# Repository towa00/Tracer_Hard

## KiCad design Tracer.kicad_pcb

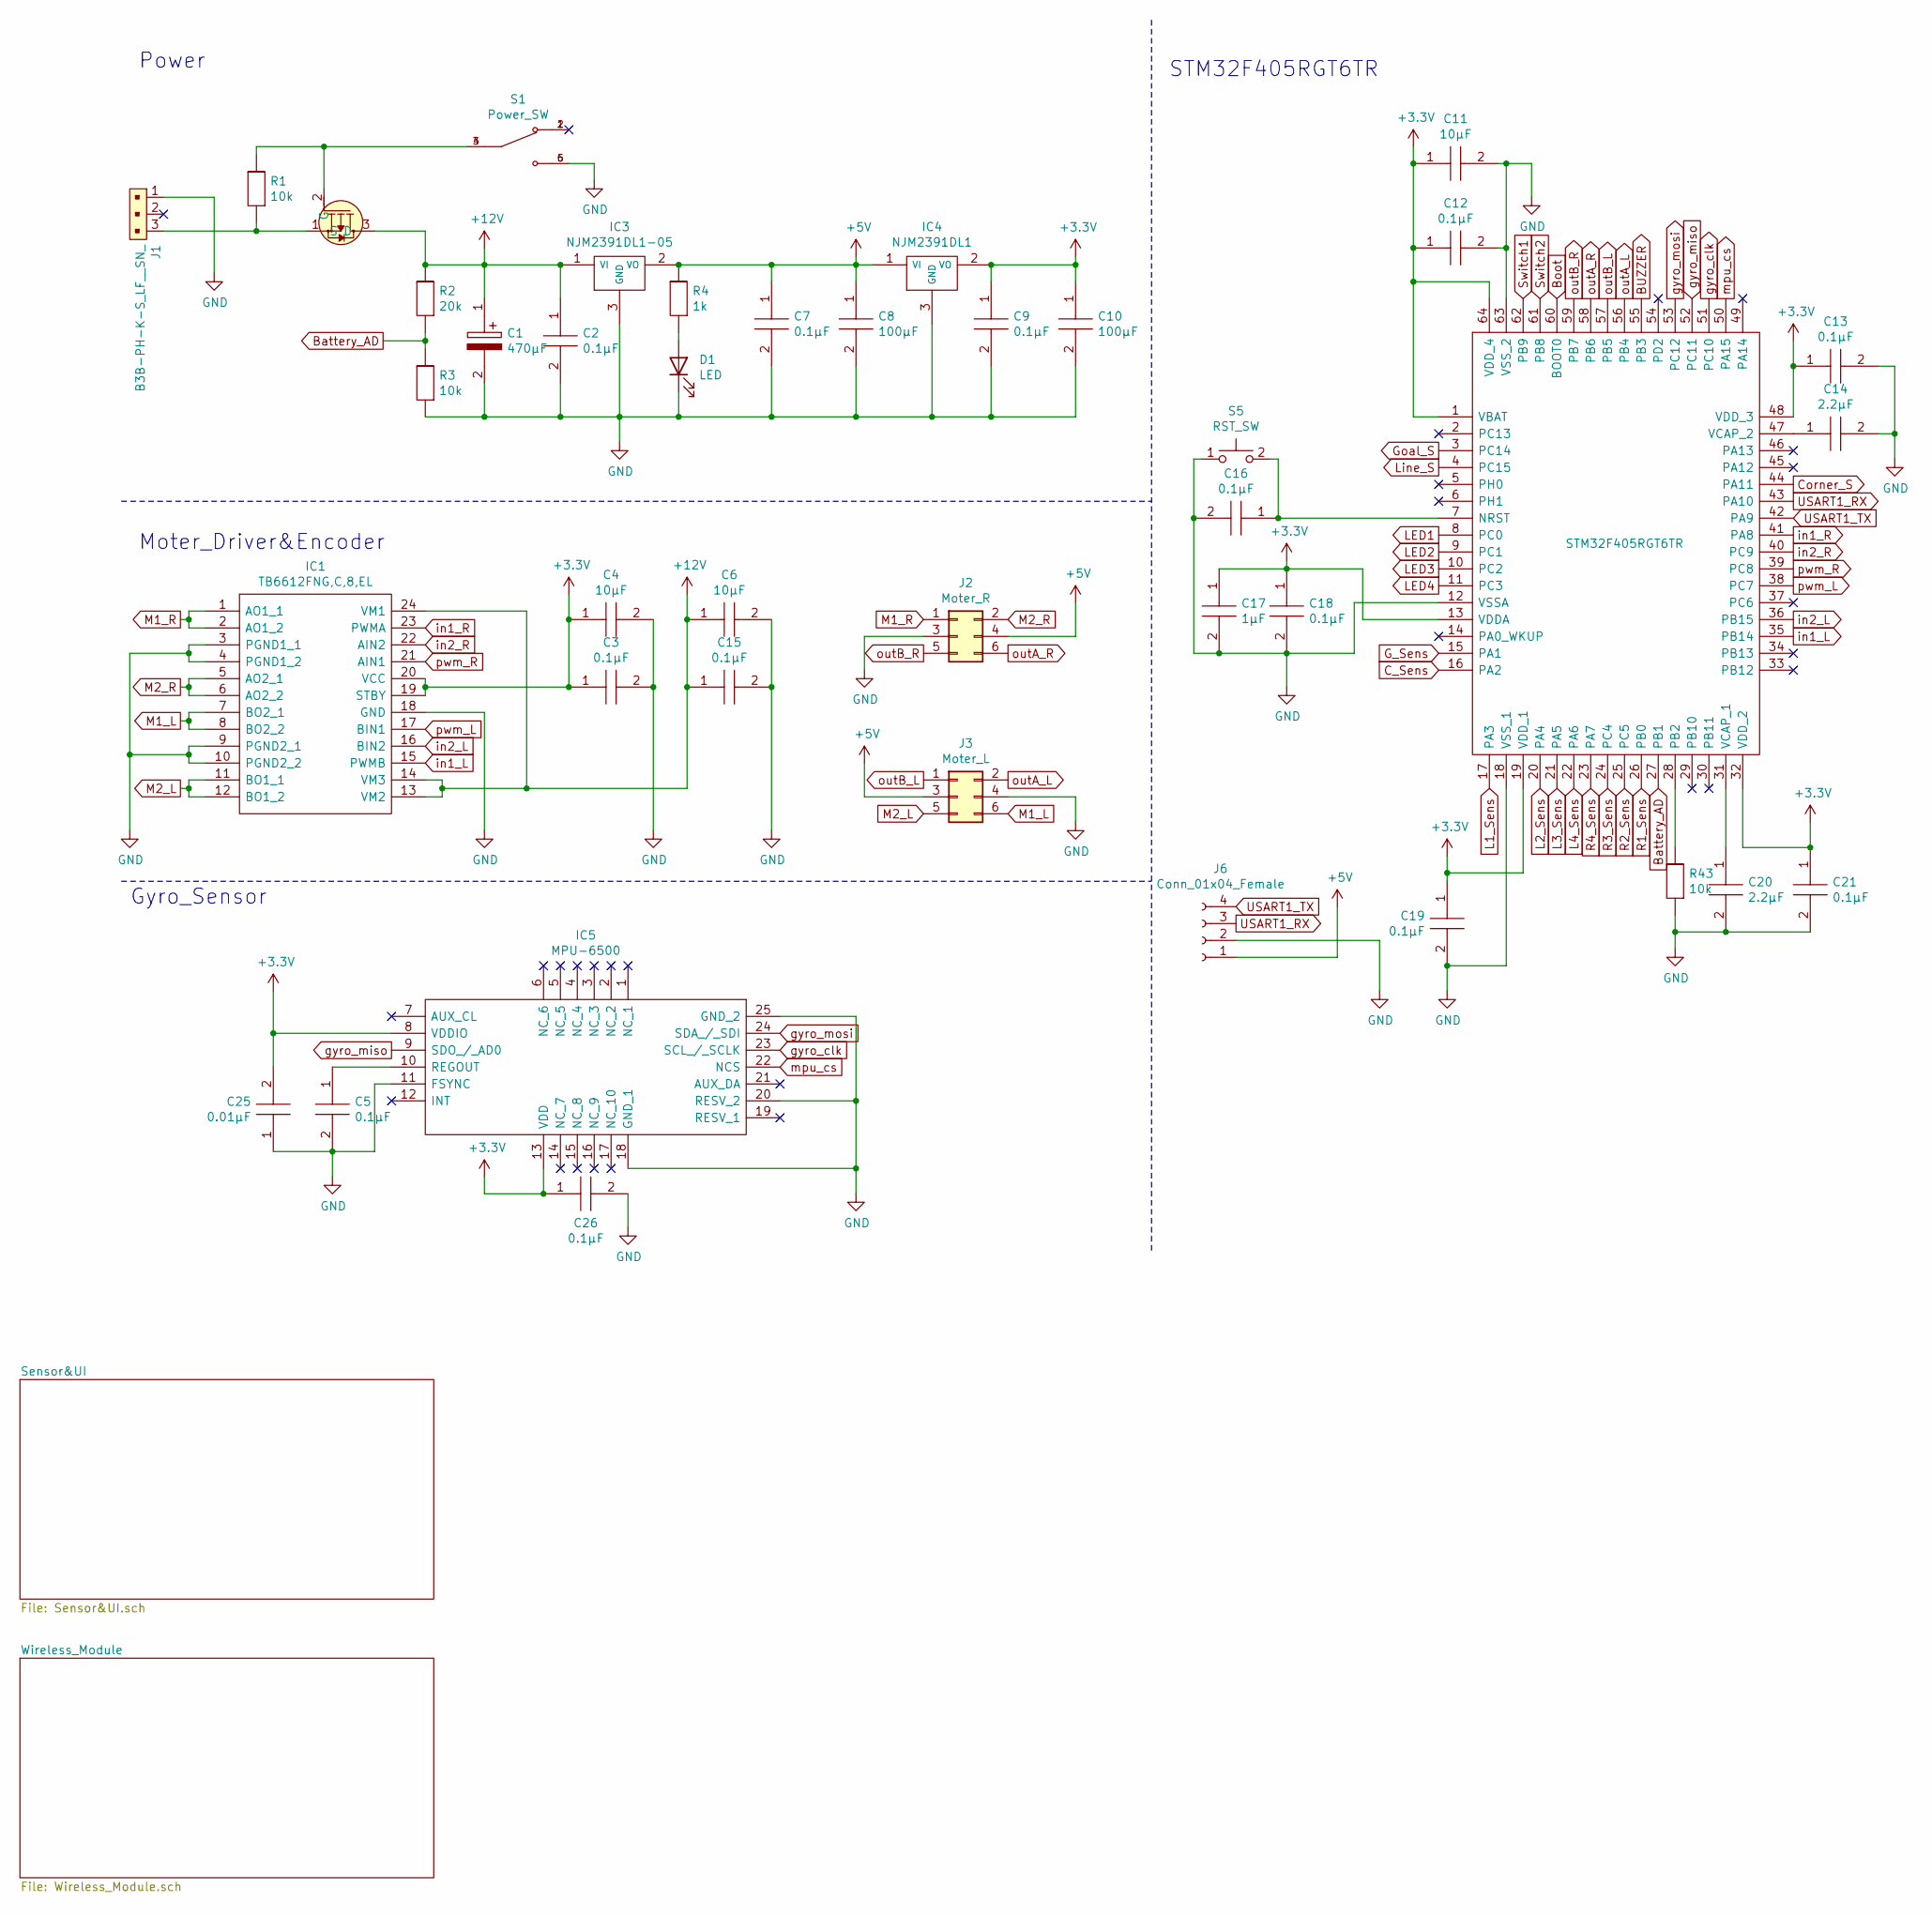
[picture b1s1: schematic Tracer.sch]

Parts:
C1: 470μF; CAPPRD500W65D1000H1300; Mouser Part Number 667-16SEPC470M
C2, C3, C5, C7, C9, C12, C13, C15, C16, C18, C19, C21, C26: 0.1μF; CAPC1608X90N; Mouser Part Number 81-GRM188R72A104KA35
C4, C6, C11: 10μF; CAPC1608X90N; Mouser Part Number 81-GRM188R6YA106MA3D
C8, C10: 100μF; CAPC3216X180N; Mouser Part Number 81-GRM31CR61A107MA8K
C14, C20: 2.2μF; CAPC1608X90N; Mouser Part Number 81-GRM188R6YA106MA3D
C17: 1μF; CAPC1608X90N; Mouser Part Number 81-GRM188R72A104KA35
C25: 0.01μF; CAPC1608X90N; Mouser Part Number 81-GRM188R72A104KA35
D1: LED; LED_0805_2012Metric
IC1: TB6612FNG,C,8,EL; SOP65P760X160-24N; Mouser Part Number 757-TB6612FNGC8EL
IC2: FDS6576; SOIC127P600X175-8N; Mouser Part Number 512-FDS6576
IC3: NJM2391DL1-05; TO-252-3-L1; Mouser Part Number 513-NJM2391DL133-TE1
IC4: NJM2391DL1; TO-252-3-L1; Mouser Part Number 513-NJM2391DL133-TE1
IC5: MPU-6500; QFN40P300X300X95-25N-D; Mouser Part Number 410-MPU-6500
IC6: STM32F405RGT6TR; QFP50P1200X1200X160-64N; Mouser Part Number 511-STM32F405RGT6TR
J1: B3B-PH-K-S_LF__SN_; PinHeader_1x3_P2mm_Drill1mm; MPN B3B-PH-K-S(LF)(SN); Digi-Key_PN 455-1705-ND
J2: Moter_R; PinHeader_2x03_P2.54mm_Vertical
J3: Moter_L; PinHeader_2x03_P2.54mm_Vertical
J6: Conn_01x04_Female; PinSocket_1x04_P2.54mm_Vertical
R1, R3, R43: 10k; RESC2012X50N
R2: 20k; RESC2012X50N
R4: 1k; RESC2012X50N
S1: Power_SW; SW_MHSS1104; PARTREV A
S5: RST_SW; SMT_4.2X3.2_; Mouser Part Number 688-SKRPACE010

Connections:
+3V3: C3.1, C4.1, C9.1, C10.1, C11.1, C12.1, C13.1, C17.1, C18.1, C19.1, C21.1, C25.2, C26.1, IC1.19 (STBY), IC1.20 (VCC), IC4.2 (VO), IC5.8 (VDDIO), IC5.13 (VDD), IC6.1 (VBAT), IC6.13 (VDDA), IC6.19 (VDD_1), IC6.32 (VDD_2), IC6.48 (VDD_3), IC6.64 (VDD_4); also elsewhere on the board
+5V: C7.1, C8.1, IC3.2 (VO), IC4.1 (VI), J2.4, J3.3, J6.1, R4.1; also elsewhere on the board
+12V: C1.1, C2.1, C6.1, C15.1, IC1.13 (VM2), IC1.14 (VM3), IC1.24 (VM1), IC2.3 (D), IC3.1 (VI), R2.1
BUZZER: IC6.55 (PB3); also elsewhere on the board
Battery_AD: IC6.27 (PB1), R2.2, R3.1
Boot: IC6.60 (BOOT0), IC6.61 (PB8); also elsewhere on the board
C_Sens: IC6.16 (PA2); also elsewhere on the board
Corner_S: IC6.44 (PA11); also elsewhere on the board
GND: C1.2, C2.2, C3.2, C4.2, C5.2, C6.2, C7.2, C8.2, C9.2, C10.2, C11.2, C12.2, C13.2, C14.2, C15.2, C16.2, C17.2, C18.2, C19.2, C20.2, C21.2, C25.1, C26.2, D1.1 (K), IC1.3 (PGND1_1), IC1.4 (PGND1_2), IC1.9 (PGND2_1), IC1.10 (PGND2_2), IC1.18 (GND), IC3.3 (GND), IC4.3 (GND), IC5.11 (FSYNC), IC5.18 (GND_1), IC5.20 (RESV_2), IC5.25 (GND_2), IC6.12 (VSSA), IC6.18 (VSS_1), IC6.63 (VSS_2), J1.1, J2.3, J3.4, J6.2, R3.2, R43.2, S1.5, S1.6, S5.1; also elsewhere on the board
G_Sens: IC6.15 (PA1); also elsewhere on the board
Goal_S: IC6.3 (PC14); also elsewhere on the board
L1_Sens: IC6.17 (PA3); also elsewhere on the board
L2_Sens: IC6.20 (PA4); also elsewhere on the board
L3_Sens: IC6.21 (PA5); also elsewhere on the board
L4_Sens: IC6.22 (PA6); also elsewhere on the board
LED1: IC6.8 (PC0); also elsewhere on the board
LED2: IC6.9 (PC1); also elsewhere on the board
LED3: IC6.10 (PC2); also elsewhere on the board
LED4: IC6.11 (PC3); also elsewhere on the board
Line_S: IC6.4 (PC15); also elsewhere on the board
M1_L: IC1.7 (BO2_1), IC1.8 (BO2_2), J3.6
M1_R: IC1.1 (AO1_1), IC1.2 (AO1_2), J2.1
M2_L: IC1.11 (BO1_1), IC1.12 (BO1_2), J3.5
M2_R: IC1.5 (AO2_1), IC1.6 (AO2_2), J2.2
unnamed: C5.1, IC5.10 (REGOUT)
unnamed: C14.1, IC6.47 (VCAP_2)
unnamed: C16.1, IC6.7 (NRST), S5.2
unnamed: C20.1, IC6.31 (VCAP_1)
unnamed: D1.2 (A), R4.2
unnamed: IC2.1 (S), J1.3, R1.2
unnamed: IC2.2 (G), R1.1, S1.3, S1.4
unnamed: IC6.28 (PB2), R43.1
unnamed: S1.1, S1.2
R1_Sens: IC6.26 (PB0); also elsewhere on the board
R2_Sens: IC6.25 (PC5); also elsewhere on the board
R3_Sens: IC6.24 (PC4); also elsewhere on the board
R4_Sens: IC6.23 (PA7); also elsewhere on the board
Switch1: IC6.62 (PB9); also elsewhere on the board
USART1_RX: IC6.43 (PA10), J6.3
USART1_TX: IC6.42 (PA9), J6.4
gyro_clk: IC5.23 (SCL_/_SCLK), IC6.51 (PC10)
gyro_miso: IC5.9 (SDO_/_AD0), IC6.52 (PC11)
gyro_mosi: IC5.24 (SDA_/_SDI), IC6.53 (PC12)
in1_L: IC1.15 (PWMB), IC6.35 (PB14)
in1_R: IC1.23 (PWMA), IC6.41 (PA8)
in2_L: IC1.16 (BIN2), IC6.36 (PB15)
in2_R: IC1.22 (AIN2), IC6.40 (PC9)
mpu_cs: IC5.22 (NCS), IC6.50 (PA15)
outA_L: IC6.56 (PB4), J3.2
outA_R: IC6.58 (PB6), J2.6
outB_L: IC6.57 (PB5), J3.1
outB_R: IC6.59 (PB7), J2.5
pwm_L: IC1.17 (BIN1), IC6.38 (PC7)
pwm_R: IC1.21 (AIN1), IC6.39 (PC8)

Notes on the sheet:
STM32F405RGT6TR
Gyro_Sensor
Moter_Driver&Encoder
Power

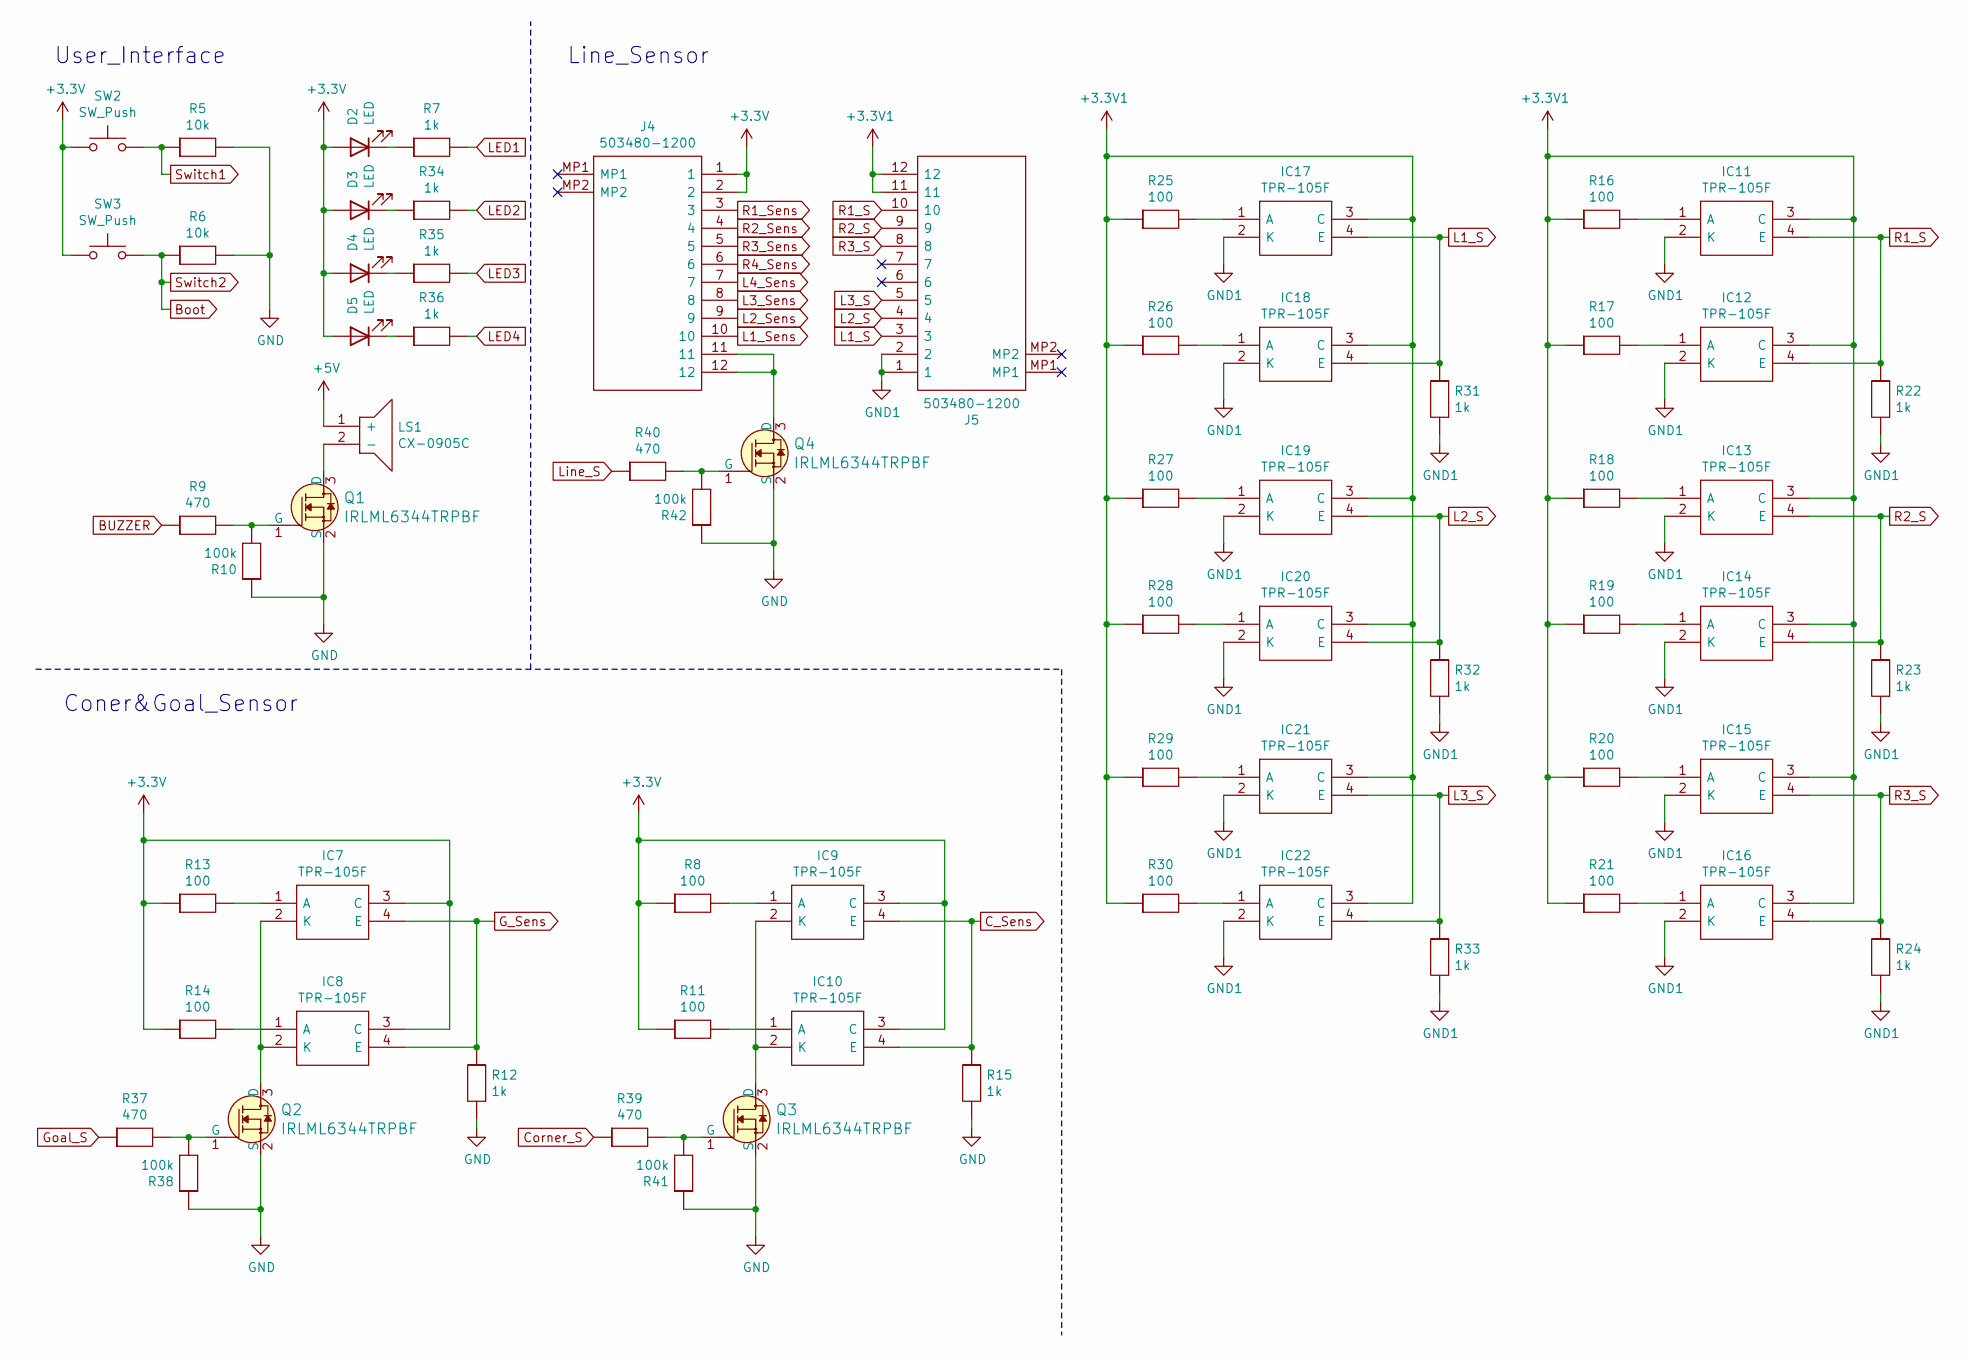
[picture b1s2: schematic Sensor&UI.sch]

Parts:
D2, D3, D4, D5: LED; LED_0805_2012Metric
IC7, IC8, IC9, IC10, IC11, IC12, IC13, IC14, IC15, IC16, IC17, IC18, IC19, IC20, IC21, IC22: TPR-105F; Mouser Part Number 512-QRE1113
J4, J5: 503480-1200; 5034801200; Mouser Part Number 538-503480-1200
LS1: CX-0905C; CX0905C; Mouser Part Number 490-CX-0905C
Q1, Q2, Q3, Q4: IRLML6344TRPBF; SOT-23-3; MPN IRLML6344TRPBF; Digi-Key_PN IRLML6344TRPBFCT-ND
R5, R6: 10k; RESC2012X50N
R7, R12, R15, R22, R23, R24, R31, R32, R33, R34, R35, R36: 1k; RESC2012X50N
R8, R11, R13, R14, R16, R17, R18, R19, R20, R21, R25, R26, R27, R28, R29, R30: 100; RESC2012X50N
R9, R37, R39, R40: 470; RESC2012X50N
R10, R38, R41, R42: 100k; RESC2012X50N
SW2, SW3: SW_Push; TVBP06-B043CW-B

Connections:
+3.3V1: IC11.3 (C), IC12.3 (C), IC13.3 (C), IC14.3 (C), IC15.3 (C), IC16.3 (C), IC17.3 (C), IC18.3 (C), IC19.3 (C), IC20.3 (C), IC21.3 (C), IC22.3 (C), J5.11, J5.12, R16.1, R17.1, R18.1, R19.1, R20.1, R21.1, R25.1, R26.1, R27.1, R28.1, R29.1, R30.1
+3V3: D2.2 (A), D3.2 (A), D4.2 (A), D5.2 (A), IC7.3 (C), IC8.3 (C), IC9.3 (C), IC10.3 (C), J4.1, J4.2, R8.1, R11.1, R13.1, R14.1, SW2.1, SW3.1; also elsewhere on the board
+5V: LS1.1 (+); also elsewhere on the board
BUZZER: R9.1; also elsewhere on the board
Boot: R6.1, SW3.2; also elsewhere on the board
C_Sens: IC9.4 (E), IC10.4 (E), R15.1; also elsewhere on the board
Corner_S: R39.1; also elsewhere on the board
GND: Q1.2 (S), Q2.2 (S), Q3.2 (S), Q4.2 (S), R5.2, R6.2, R10.1, R12.2, R15.2, R38.1, R41.1, R42.1; also elsewhere on the board
GND1: IC11.2 (K), IC12.2 (K), IC13.2 (K), IC14.2 (K), IC15.2 (K), IC16.2 (K), IC17.2 (K), IC18.2 (K), IC19.2 (K), IC20.2 (K), IC21.2 (K), IC22.2 (K), J5.1, J5.2, R22.2, R23.2, R24.2, R31.2, R32.2, R33.2
G_Sens: IC7.4 (E), IC8.4 (E), R12.1; also elsewhere on the board
Goal_S: R37.1; also elsewhere on the board
L1_S: IC17.4 (E), IC18.4 (E), J5.3, R31.1
L1_Sens: J4.10; also elsewhere on the board
L2_S: IC19.4 (E), IC20.4 (E), J5.4, R32.1
L2_Sens: J4.9; also elsewhere on the board
L3_S: IC21.4 (E), IC22.4 (E), J5.5, R33.1
L3_Sens: J4.8; also elsewhere on the board
L4_Sens: J4.7; also elsewhere on the board
LED1: R7.2; also elsewhere on the board
LED2: R34.2; also elsewhere on the board
LED3: R35.2; also elsewhere on the board
LED4: R36.2; also elsewhere on the board
Line_S: R40.1; also elsewhere on the board
unnamed: D2.1 (K), R7.1
unnamed: D3.1 (K), R34.1
unnamed: D4.1 (K), R35.1
unnamed: D5.1 (K), R36.1
unnamed: IC7.1 (A), R13.2
unnamed: IC7.2 (K), IC8.2 (K), Q2.3 (D)
unnamed: IC8.1 (A), R14.2
unnamed: IC9.1 (A), R8.2
unnamed: IC10.1 (A), R11.2
unnamed: IC9.2 (K), IC10.2 (K), Q3.3 (D)
unnamed: IC11.1 (A), R16.2
unnamed: IC12.1 (A), R17.2
unnamed: IC13.1 (A), R18.2
unnamed: IC14.1 (A), R19.2
unnamed: IC15.1 (A), R20.2
unnamed: IC16.1 (A), R21.2
unnamed: IC17.1 (A), R25.2
unnamed: IC18.1 (A), R26.2
unnamed: IC19.1 (A), R27.2
unnamed: IC20.1 (A), R28.2
unnamed: IC21.1 (A), R29.2
unnamed: IC22.1 (A), R30.2
unnamed: J4.11, J4.12, Q4.3 (D)
unnamed: LS1.2 (-), Q1.3 (D)
unnamed: Q1.1 (G), R9.2, R10.2
unnamed: Q2.1 (G), R37.2, R38.2
unnamed: Q3.1 (G), R39.2, R41.2
unnamed: Q4.1 (G), R40.2, R42.2
R1_S: IC11.4 (E), IC12.4 (E), J5.10, R22.1
R1_Sens: J4.3; also elsewhere on the board
R2_S: IC13.4 (E), IC14.4 (E), J5.9, R23.1
R2_Sens: J4.4; also elsewhere on the board
R3_S: IC15.4 (E), IC16.4 (E), J5.8, R24.1
R3_Sens: J4.5; also elsewhere on the board
R4_Sens: J4.6; also elsewhere on the board
Switch1: R5.1, SW2.2; also elsewhere on the board

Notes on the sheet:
User_Interface
Line_Sensor
Coner&Goal_Sensor

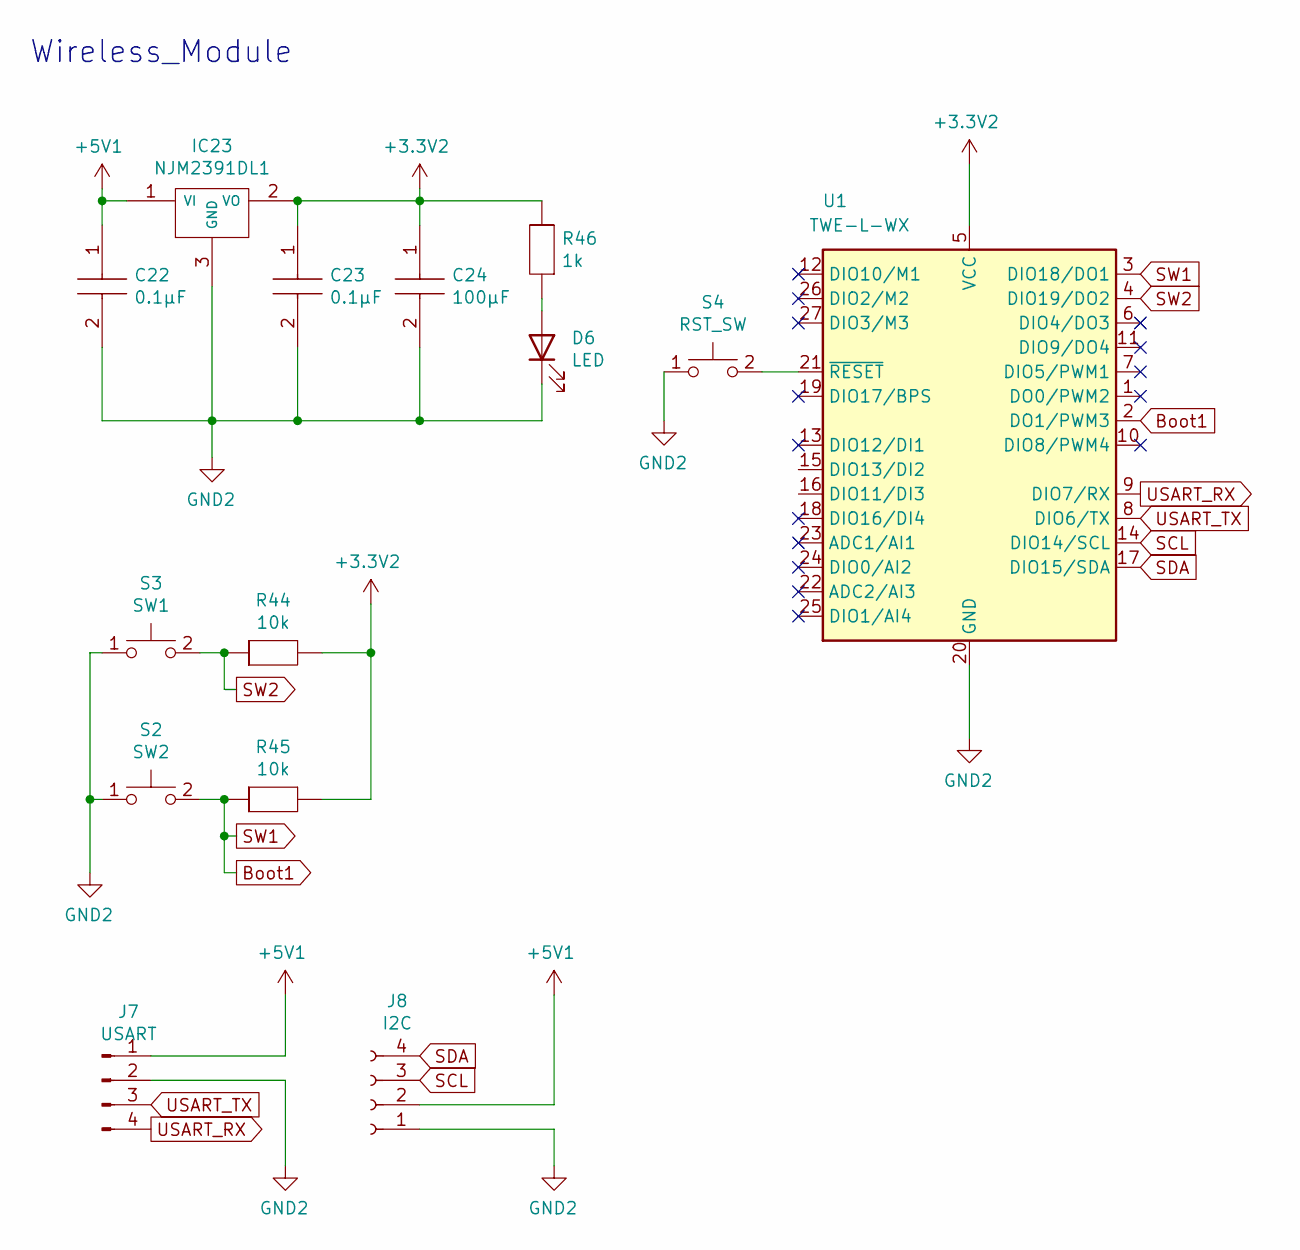
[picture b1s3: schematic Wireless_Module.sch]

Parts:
C22, C23: 0.1μF; CAPC1608X90N; Mouser Part Number 81-GRM188R72A104KA35
C24: 100μF; CAPC3216X180N; Mouser Part Number 81-GRM31CR61A107MA8K
D6: LED; LED_0805_2012Metric
IC23: NJM2391DL1; TO-252-3-L1; Mouser Part Number 513-NJM2391DL133-TE1
J7: USART; PinHeader_1x04_P2.54mm_Vertical
J8: I2C; PinSocket_1x04_P2.54mm_Vertical
R44, R45: 10k; RESC2012X50N
R46: 1k; RESC2012X50N
S2: SW2; SMT_4.2X3.2_; Mouser Part Number 688-SKRPACE010
S3: SW1; SMT_4.2X3.2_; Mouser Part Number 688-SKRPACE010
S4: RST_SW; SMT_4.2X3.2_; Mouser Part Number 688-SKRPACE010
U1: TWE-L-WX; MonoWireless_TWE-L-WX

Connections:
+3.3V_1: C23.1, C24.1, IC23.2 (VO), R44.2, R45.2, R46.1, U1.5 (VCC)
+5V1: C22.1, IC23.1 (VI), J7.1, J8.2
Boot1: R45.1, S2.2, U1.2 (DO1/PWM3), U1.3 (DIO18/DO1)
GND2: C22.2, C23.2, C24.2, D6.1 (K), IC23.3 (GND), J7.2, J8.1, S2.1, S3.1, S4.1, U1.20 (GND), U1.28 (GND), U1.30 (GND), U1.31 (GND), U1.32 (GND)
unnamed: D6.2 (A), R46.2
unnamed: S4.2, U1.21 (~RESET)
SCL: J8.3, U1.14 (DIO14/SCL)
SDA: J8.4, U1.17 (DIO15/SDA)
SW2: R44.1, S3.2, U1.4 (DIO19/DO2)
USART_RX: J7.4, U1.9 (DIO7/RX)
USART_TX: J7.3, U1.8 (DIO6/TX)

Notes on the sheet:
Wireless_Module

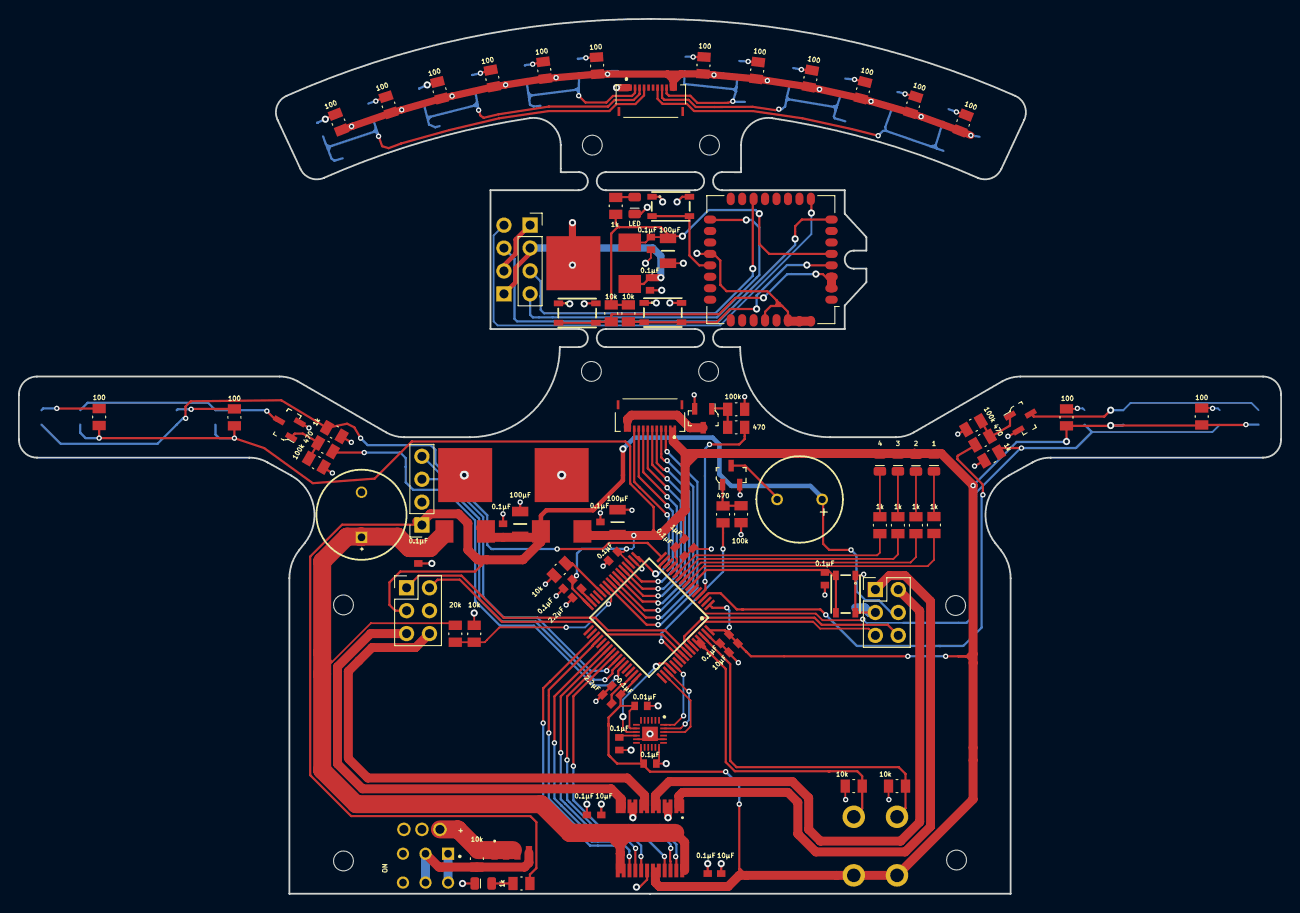
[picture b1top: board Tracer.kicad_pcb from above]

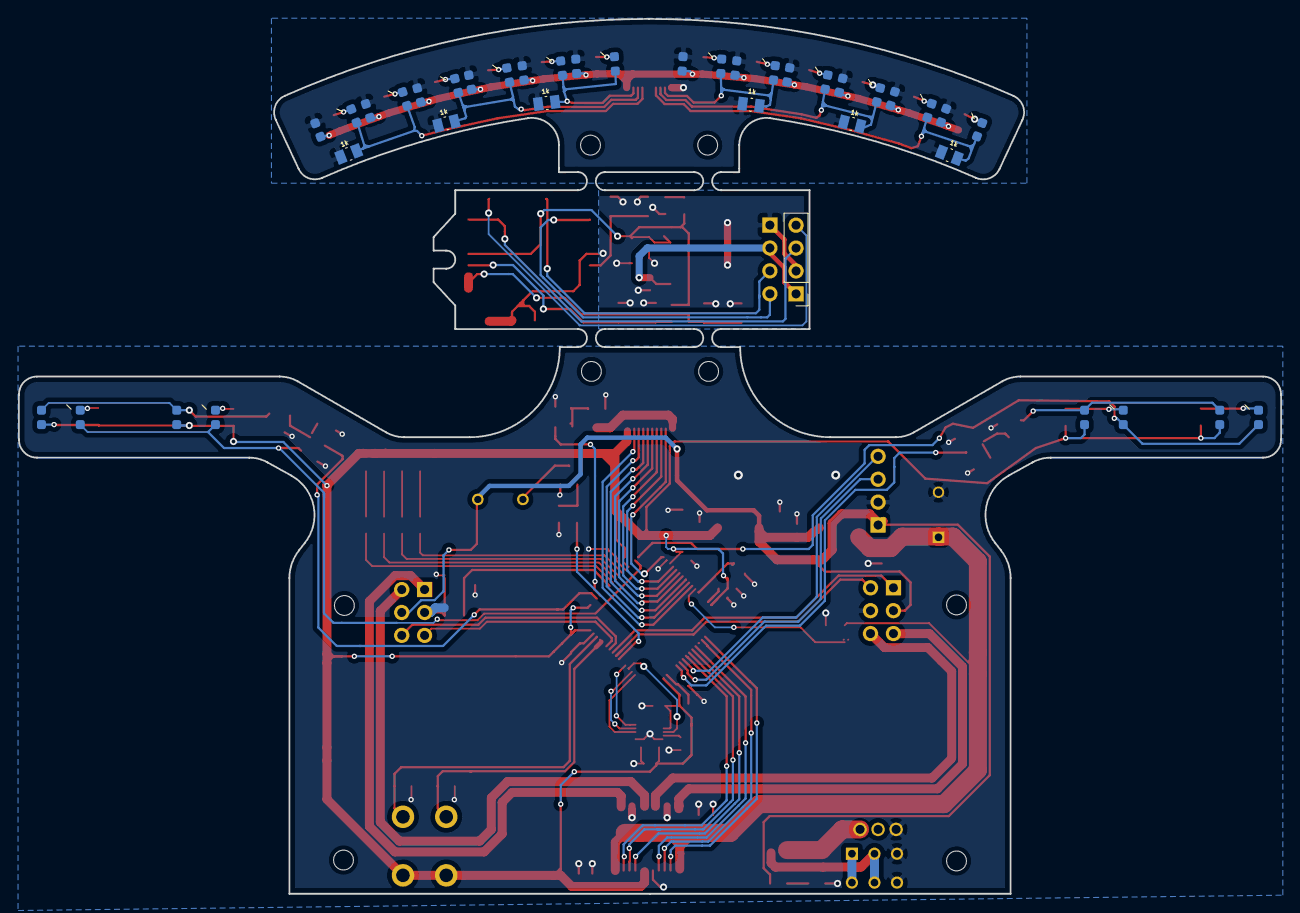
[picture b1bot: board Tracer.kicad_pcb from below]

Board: 2 copper layers, 140.0 x 97.0 mm, 130 parts (23 on the bottom side), 101 nets.

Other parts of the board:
M2, M2#2, M2#3, M2#4, M2#5, M2#6, M2#7, M2#8: MountingHole_2.2mm_M2

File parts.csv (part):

Reference, Quantity, Value, Footprint, Datasheet, Description, Height, Manufacturer_Name, Manufacturer_Part_Number, Mouser Part Number, Mouser Price/Stock, MANUFACTURER, MAXIMUM_PACKAGE_HEIGHT, PARTREV, STANDARD, Category, DK_Datasheet_Link, DK_Detail_Page, Digi-Key_PN, Family, MPN, Manufacturer, Status
C1 ,1,"470μF","CAPPRD500W65D1000H1300","http://industrial.panasonic.com/cdbs/www-data/pdf/AAB8000/AA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","Panasonic 470uF 16 V dc Polymer Aluminium Electrolytic Capacitor F13, OS-CON Series 5000h 10 x 13mm","13","Panasonic","16SEPC470M","667-16SEPC470M","https://www.mouser.co.uk/ProductDetail/Panasonic/16SEPC470M?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","","","","","","","","","","","",""
C8 C10 C24 ,3,"100μF","GRM31CR61A107MEA8K:CAPC3216X180N","http://www.murata.com/~/media/webrenewal/support/library/cat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","Multilayer Ceramic Capacitors MLCC - SMD/SMT 100UF    10V   20%        3216","1.8","Murata Electronics","GRM31CR61A107MEA8K","81-GRM31CR61A107MA8K","https://www.mouser.co.uk/ProductDetail/Murata-Electronics/GR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","","","","","","","","","","","",""
C14 C20 ,2,"2.2μF","CAPC1608X90N","http://componentsearchengine.com/Datasheets/1/GRM188R6YA106M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","Multilayer Ceramic Capacitors MLCC - SMD/SMT 0603 10uF 35volts *Derate Voltage/Temp","0.9","Murata Electronics","GRM188R6YA106MA73D","81-GRM188R6YA106MA3D","https://www.mouser.co.uk/ProductDetail/Murata-Electronics/GR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","","","","","","","","","","","",""
C2 C3 C5 C7 C9 C12 C13 C15 C16 C18 C19 C21 C22 C23 C26 ,15,"0.1μF","CAPC1608X90N","https://datasheet.datasheetarchive.com/originals/distributor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","Murata 0603 (1608M) 100nF MLCC 100V dc +/-10% SMD GRM188R72A104KA35D","0.9","Murata Electronics","GRM188R72A104KA35D","81-GRM188R72A104KA35","https://www.mouser.co.uk/ProductDetail/Murata-Electronics/GR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","","","","","","","","","","","",""
C17 ,1,"1μF","CAPC1608X90N","https://datasheet.datasheetarchive.com/originals/distributor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","Murata 0603 (1608M) 100nF MLCC 100V dc +/-10% SMD GRM188R72A104KA35D","0.9","Murata Electronics","GRM188R72A104KA35D","81-GRM188R72A104KA35","https://www.mouser.co.uk/ProductDetail/Murata-Electronics/GR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","","","","","","","","","","","",""
C25 ,1,"0.01μF","CAPC1608X90N","https://datasheet.datasheetarchive.com/originals/distributor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","Murata 0603 (1608M) 100nF MLCC 100V dc +/-10% SMD GRM188R72A104KA35D","0.9","Murata Electronics","GRM188R72A104KA35D","81-GRM188R72A104KA35","https://www.mouser.co.uk/ProductDetail/Murata-Electronics/GR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","","","","","","","","","","","",""
C4 C6 C11 ,3,"10μF","CAPC1608X90N","http://componentsearchengine.com/Datasheets/1/GRM188R6YA106M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","Multilayer Ceramic Capacitors MLCC - SMD/SMT 0603 10uF 35volts *Derate Voltage/Temp","0.9","Murata Electronics","GRM188R6YA106MA73D","81-GRM188R6YA106MA3D","https://www.mouser.co.uk/ProductDetail/Murata-Electronics/GR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","","","","","","","","","","","",""
D1 D6 ,2,"LED","LED_SMD:LED_0805_2012Metric","~"
D2 ,1,"LED1","LED_SMD:LED_1206_3216Metric","http://www.everlight.com/file/ProductFile/IR26-21C-L110-TR8.pdf"
D3 ,1,"LED2","LED_SMD:LED_1206_3216Metric","http://www.everlight.com/file/ProductFile/IR26-21C-L110-TR8.pdf"
D4 ,1,"LED3","LED_SMD:LED_1206_3216Metric","http://www.everlight.com/file/ProductFile/IR26-21C-L110-TR8.pdf"
D5 ,1,"LED4","LED_SMD:LED_1206_3216Metric","http://www.everlight.com/file/ProductFile/IR26-21C-L110-TR8.pdf"
IC1 ,1,"TB6612FNG,C,8,EL","TB6612FNG:SOP65P760X160-24N","http://toshiba.semicon-storage.com/info/docget.jsp?did=10660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","otor / Motion / Ignition Controllers & Drivers Brush Motor Driver IC","1.6","Toshiba","TB6612FNG,C,8,EL","757-TB6612FNGC8EL","https://www.mouser.co.uk/ProductDetail/Toshiba/TB6612FNGC8EL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","","","","","","","","","","","",""
IC7 IC8 IC9 IC10 IC11 IC12 IC13 IC14 IC15 IC16 IC17 IC18 IC19 IC20 IC21 IC22 ,16,"TPR-105F","TPR-105F:TPR-105F","https://www.onsemi.com/pub/Collateral/QRE1113-D.PDF","Miniature Reflective Object Sensor","1.7","onsemi","TPR-105","512-QRE1113","https://www.mouser.co.uk/ProductDetail/onsemi-Fairchild/QRE1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","","","","","","","","","","","",""
IC2 ,1,"FDS6576","FDS6576:SOIC127P600X175-8N","https://www.onsemi.com/pub/Collateral/751EB.PDF","FDS6576, P-channel MOSFET Transistor 11 A 20 V, 8-Pin SOIC","1.75","onsemi","FDS6576","512-FDS6576","https://www.mouser.co.uk/ProductDetail/ON-Semiconductor-Fair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","","","","","","","","","","","",""
IC3 ,1,"NJM2391DL1-05","NJM2391DL1-33-TE1:TO-252-3-L1","","LDO Voltage Regulators LDO","","New Japan Radio","NJM2391DL1-33-TE1","513-NJM2391DL133-TE1","https://www.mouser.co.uk/ProductDetail/NJR/NJM2391DL1-33-TE1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","","","","","","","","","","","",""
IC4 IC23 ,2,"NJM2391DL1","NJM2391DL1-33-TE1:TO-252-3-L1","","LDO Voltage Regulators LDO","","New Japan Radio","NJM2391DL1-33-TE1","513-NJM2391DL133-TE1","https://www.mouser.co.uk/ProductDetail/NJR/NJM2391DL1-33-TE1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","","","","","","","","","","","",""
IC5 ,1,"MPU-6500","MPU-6500:QFN40P300X300X95-25N-D","https://product.tdk.com/system/files/dam/doc/product/sensor/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","IMUs - Inertial Measurement Units 6-Axis MEMS MotionTracking  Device with DMP","0.95","TDK","MPU-6500","410-MPU-6500","https://www.mouser.co.uk/ProductDetail/TDK-InvenSense/MPU-65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","","","","","","","","","","","",""
IC6 ,1,"STM32F405RGT6TR","STM32F405RGT6TR:QFP50P1200X1200X160-64N","http://www.st.com/web/en/resource/technical/document/datashe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","STM32F405RGT6TR, 32 bit ARM Cortex M4 MCU 168MHz 1024 kB Flash, 192 kB RAM, 2xUSB CAN I2C 64-Pin LQFP","1.6","STMicroelectronics","STM32F405RGT6TR","511-STM32F405RGT6TR","https://www.mouser.co.uk/ProductDetail/STMicroelectronics/ST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","","","","","","","","","","","",""
J1 ,1,"B3B-PH-K-S_LF__SN_","digikey-footprints:PinHeader_1x3_P2mm_Drill1mm","http://www.jst-mfg.com/product/pdf/eng/ePH.pdf","CONN HEADER VERT 3POS 2MM","","","","","","","","","","Connectors, Interconnects","http://www.jst-mfg.com/product/pdf/eng/ePH.pdf","/product-detail/en/jst-sales-america-inc/B3B-PH-K-S(LF)(SN)/455-1705-ND/926612","455-1705-ND","Rectangular Connectors - Headers, Male Pins","B3B-PH-K-S(LF)(SN)","JST Sales America Inc.","Active"
J2 ,1,"Moter_R","Connector_PinHeader_2.54mm:PinHeader_2x03_P2.54mm_Vertical","~"
J3 ,1,"Moter_L","Connector_PinHeader_2.54mm:PinHeader_2x03_P2.54mm_Vertical","~"
J4 J5 ,2,"503480-1200","503480-1200:5034801200","https://datasheet.datasheetarchive.com/originals/distributor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","FFC & FPC Connectors .5mm FPC 12P CONN RA SMT B-FLIP DUAL","1.3","Molex","503480-1200","538-503480-1200","https://www.mouser.co.uk/ProductDetail/Molex/503480-1200?qs=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","","","","","","","","","","","",""
J6 ,1,"Conn_01x04_Female","Connector_PinSocket_2.54mm:PinSocket_1x04_P2.54mm_Vertical","~"
J7 ,1,"USART","Connector_PinHeader_2.54mm:PinHeader_1x04_P2.54mm_Vertical","~"
J8 ,1,"I2C","Connector_PinSocket_2.54mm:PinSocket_1x04_P2.54mm_Vertical","~"
LS1 ,1,"CX-0905C","CX-0905C:CX0905C","https://www.cuidevices.com/product/resource/digikeypdf/cx-0905c.pdf","Piezo Buzzers & Audio Indicators Buzzers","5.5","CUI Devices","CX-0905C","490-CX-0905C","https://www.mouser.co.uk/ProductDetail/CUI-Devices/CX-0905C?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","","","","","","","","","","","",""
Q1 Q2 Q3 Q4 ,4,"IRLML6344TRPBF","digikey-footprints:SOT-23-3","https://www.infineon.com/dgdl/irlml6344pbf.pdf?fileId=5546d4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","MOSFET N-CH 30V 5A SOT23","","","","","","","","","","Discrete Semiconductor Products","https://www.infineon.com/dgdl/irlml6344pbf.pdf?fileId=5546d4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","/product-detail/en/infineon-technologies/IRLML6344TRPBF/IRLML6344TRPBFCT-ND/2538168","IRLML6344TRPBFCT-ND","Transistors - FETs, MOSFETs - Single","IRLML6344TRPBF","Infineon Technologies","Active"
R1 R3 R5 R6 R43 R44 R45 ,7,"10k","RG2012N-103-B-T5:RESC2012X50N",""
R2 ,1,"20k","RG2012N-103-B-T5:RESC2012X50N",""
R8 R11 R13 R14 R16 R17 R18 R19 R20 R21 R25 R26 R27 R28 R29 R30 ,16,"100","RG2012N-103-B-T5:RESC2012X50N",""
R9 R37 R39 R40 ,4,"470","RG2012N-103-B-T5:RESC2012X50N",""
R10 R38 R41 R42 ,4,"100k","RG2012N-103-B-T5:RESC2012X50N",""
R4 R7 R12 R15 R22 R23 R24 R31 R32 R33 R34 R35 R36 R46 ,14,"1k","RG2012N-103-B-T5:RESC2012X50N",""
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
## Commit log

2023-11-23 [追加]トレーサ回路図
